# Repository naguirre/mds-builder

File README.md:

# Manufacture du Son

Open-source network audio player firmware. The board is built around an Allwinner **F1C200s** SoC running Linux and an **ESP32-C3** companion chip handling Wi-Fi and BLE. Audio is routed out over SPDIF.

📖 **Full documentation**: <https://naguirre.github.io/mds-builder/>

## Quick start

```sh
make build              # build firmware natively (Buildroot)
make build CONTAINER=1  # build inside the Docker container
```

Output images land in `output/images/`. See the [flashing guide](https://naguirre.github.io/mds-builder/flashing/) for getting them onto a board.

## Repository layout

- `buildroot_config/` — Buildroot defconfigs per machine
- `mds_external/` — `BR2_EXTERNAL` tree (boards, packages, overlays, FIT image)
- `mds-hardware/` — KiCad sources (see [mds-hardware/README.md](mds-hardware/README.md))
- `doc/` — Zola site, source for the published docs
- `src/esp-hosted/` — vendored ESP-Hosted sources

## Browsing the docs locally

```sh
cd doc && zola serve
```

## Hardware

The KiCad projects and PCB versions (v1, v1.1, v2) live under [`mds-hardware/`](mds-hardware/README.md). Schematics, PCB PDFs and gerbers are published alongside the documentation under `/hardware/<version>/`.

## License

- **Software** (this repository): MIT — see [LICENSE](LICENSE)
- **Hardware** (`mds-hardware/`): CERN-OHL-P v2 — see [mds-hardware/LICENSE](mds-hardware/LICENSE)

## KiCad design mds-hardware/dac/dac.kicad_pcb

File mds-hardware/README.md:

# mds-hardware

KiCad sources and fabrication outputs for a small network audio player board built around an Allwinner F1C200s SoC, an ESP32-C3 for Wi-Fi, NAND flash storage, an EA3036 power management IC, and an audio DAC daughter board.

The repository contains two KiCad projects:
- [network_player/](network_player/) — the main board
- [dac/](dac/) — the audio DAC daughter board

## Versions

| Version | Date       | Status                                             | Schematic | PCB | Gerbers |
|---------|------------|----------------------------------------------------|-----------|-----|---------|
| v1      | 2024-01-15 | Sent to JLCPCB, had routing issues                 | [PDF](../doc/static/hardware/v1/schematic.pdf) | [PDF](../doc/static/hardware/v1/pcb.pdf) | [ZIP](../doc/static/hardware/v1/gerbers.zip) |
| v1.1    | 2024-06-02 | Sent to JLCPCB, fixes routing issues of v1         | [PDF](../doc/static/hardware/v1.1/schematic.pdf) | [PDF](../doc/static/hardware/v1.1/pcb.pdf) | [ZIP](../doc/static/hardware/v1.1/gerbers.zip) |
| v2      | 2024-10-17 | Full redesign on Allwinner T113-s3, never produced | [PDF](../doc/static/hardware/v2/schematic.pdf) | [PDF](../doc/static/hardware/v2/pcb.pdf) | [ZIP](../doc/static/hardware/v2/gerbers.zip) |

See also the rendered [Board design](../doc/content/hardware/design.md) page in the main documentation.

References on GitHub: v1 is at commit [`c1560a5`](../../commit/c1560a5), v1.1 is the [`v1.1`](../../tree/v1.1) tag, v2 lives on the [`network_player_v2`](../../tree/network_player_v2) branch. The [`v1_jlcpcb`](../../tree/v1_jlcpcb) tag points to the JLCPCB return files for v1.

## Latest produced version: v1.1

v1.1 is the version that was actually fabricated and assembled by JLCPCB. Compared to v1, it brings the following changes (see commit [`47ae173`](../../commit/47ae173)):

- Removed the discrete transistors used for ESP32 boot/reset, driven directly from F1C200s GPIOs instead
- EA3036 enable pin tied to 3.3 V
- Added a RST button that pulls the MISO line to ground to disable booting from flash
- ESP32 moved to SPI1; SPI0 is now shared between the NAND flash and the RPi connector

### Schematic

## License

The hardware design (KiCad sources, schematics, PCB layouts and gerbers) is released under the **CERN Open Hardware Licence Version 2 — Permissive** (CERN-OHL-P v2). See [LICENSE](LICENSE).

Copyright (c) 2026 Nicolas Aguirre.

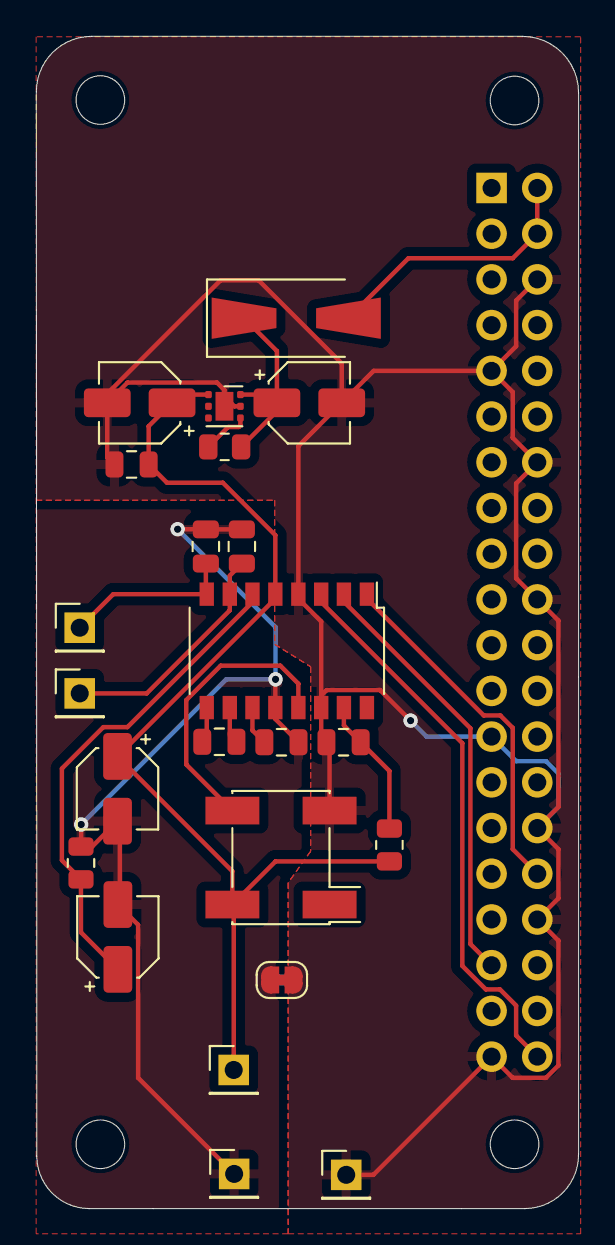
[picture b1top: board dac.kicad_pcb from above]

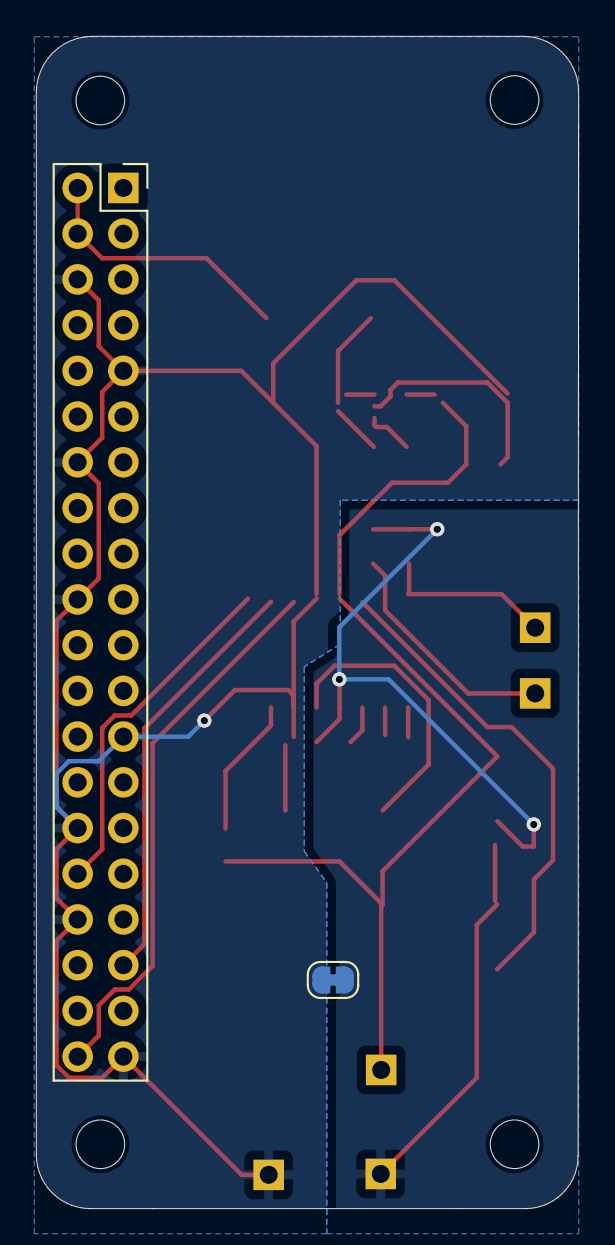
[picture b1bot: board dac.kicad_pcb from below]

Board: 2 copper layers, 30.1 x 65.1 mm, 29 parts (2 on the bottom side), 17 nets.

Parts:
C1: 2.2uF; C_0805_2012Metric
C2: 2.2uF/50V; CP_Elec_4x5.8
C3, C8, C9: 10uF/25V; CP_Elec_4x5.8
C4, C5, C10: 1uF; C_0805_2012Metric
C6, C7: 4.7nF; C_0805_2012Metric
D1: 1N5822/SS34/SMA; D_SMA-SMB_Universal_Handsoldering
H1, H2, H3, H4: MountingHole; MountingHole_2.7mm_M2.5
J1: Raspberry_Pi_2_3; PinSocket_2x20_P2.54mm_Vertical
J2: LEFT; PinHeader_1x01_P2.54mm_Vertical
J3: RIGHT; PinHeader_1x01_P2.54mm_Vertical
J6: 3v3; PinHeader_1x01_P2.54mm_Vertical
J7: GND; PinHeader_1x01_P2.54mm_Vertical
J8: GNDA; PinHeader_1x01_P2.54mm_Vertical
NT1, NT2: NetTie_2; SolderJumper-2_P1.3mm_Bridged_RoundedPad1.0x1.5mm
R1, R3: 100k; R_0805_2012Metric
R2: 220k; R_0805_2012Metric
U1: TCXO 49.152 MHz; Oscillator_SMD_Fordahl_DFAS11-4Pin_7.0x5.0mm_HandSoldering
U2: ES9023; SOP-16_4.4x10.4mm_P1.27mm
U5: LP5912-3.3DRV; WSON-6-1EP_2x2mm_P0.65mm_EP1x1.6mm

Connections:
+3V3: C2.1, C9.1, C10.1, J6.1, R1.2, U1.4 (VDD), U2.5 (AVCC), U5.1 (OUT)
+5V: D1.2 (A), J1.2 (5V), J1.4 (5V)
/AUDIO_LEFT: C7.1, J2.1, U2.7 (AOUTL)
/AUDIO_RIGHT: C6.1, J3.1, U2.8 (AOUTR)
/I2S_BCLK: J1.32 (PWM0/GPIO12), U2.1 (BCK)
/I2S_DOUT: J1.40 (GPIO21/SCLK1), U2.3 (SDI)
/I2S_LRCK: J1.35 (GPIO19/MISO1), U2.2 (LRCK)
/VIN: C8.1, D1.1 (K), R3.2, U5.6 (IN)
GND: C1.2, C8.2, C9.2, C10.2, J1.6 (GND), J1.9 (GND), J1.14 (GND), J1.20 (GND), J1.25 (GND), J1.30 (GND), J1.34 (GND), J1.39 (GND), J7.1, NT1.1, NT2.1, U1.2 (GND), U2.4 (DIF), U2.14 (DGND), U5.5 (GND), U5.7 (EP)
GNDA: C2.2, C3.2, C4.2, C6.2, C7.2, J8.1, NT1.2, NT2.2, R2.1, U2.12 (AGND)
unnamed: U1.3 (OUT), U2.13 (MCLK)
unnamed: C5.2, U2.10 (CN)
unnamed: C5.1, U2.9 (CP)
unnamed: C1.1, R1.1, U2.15 (MUTE_B)
unnamed: C4.1, U2.11 (NEG)
unnamed: C3.1, R2.2, U2.6 (VREG)
unnamed: R3.1, U5.4 (EN)

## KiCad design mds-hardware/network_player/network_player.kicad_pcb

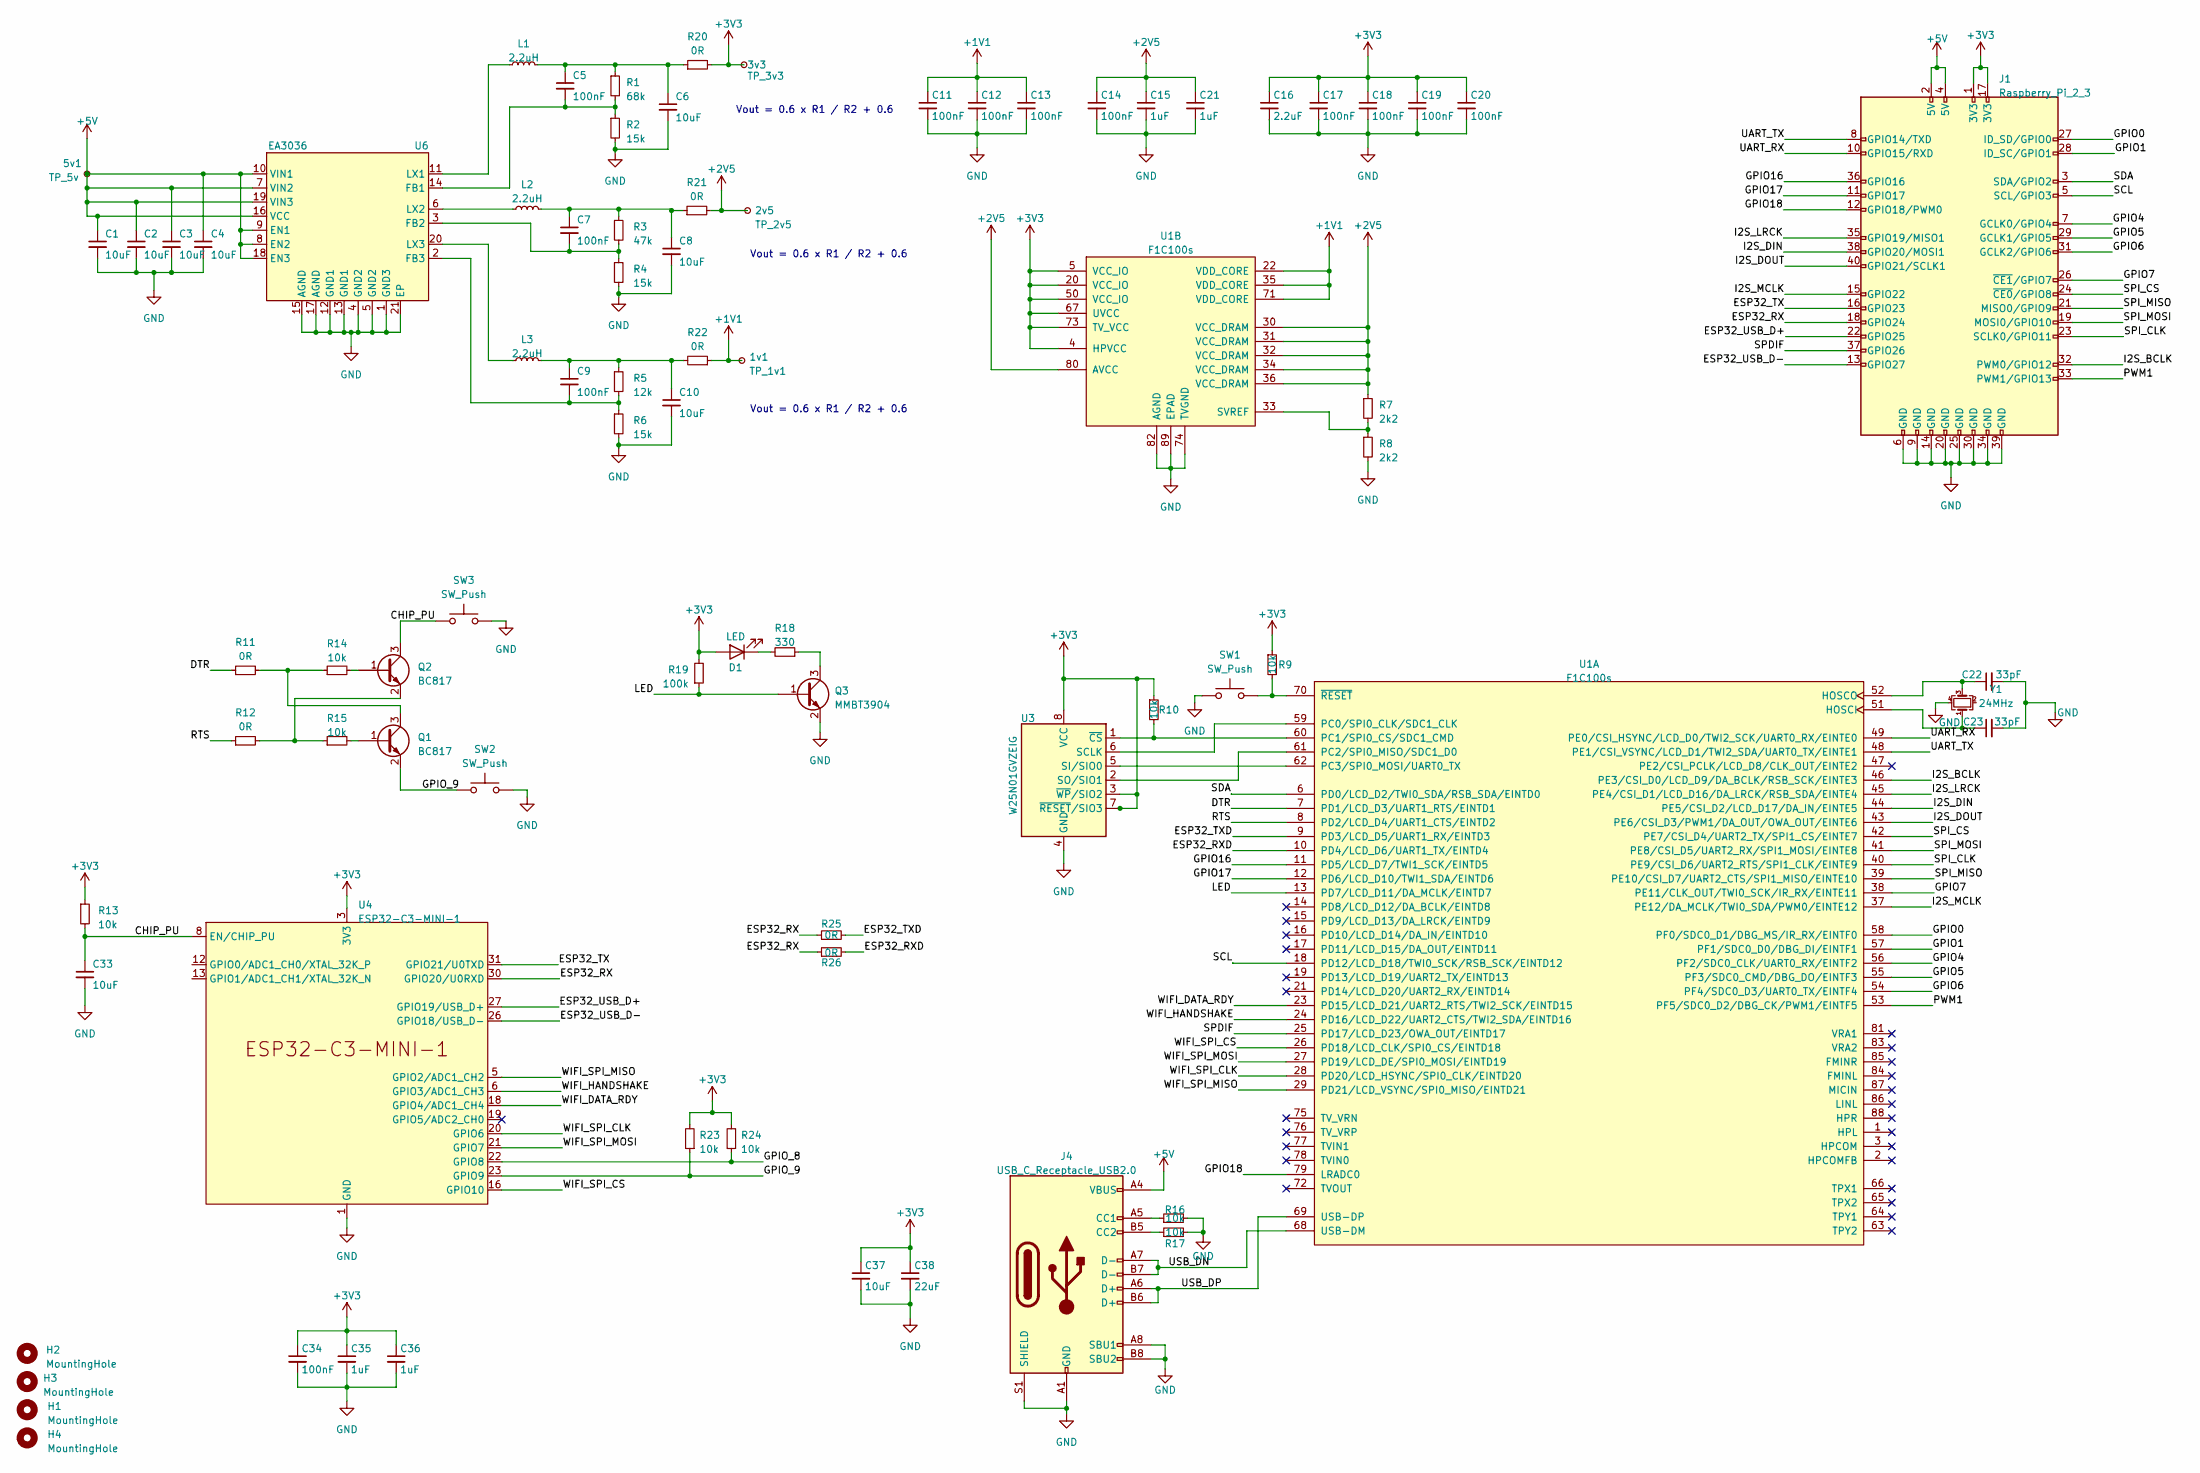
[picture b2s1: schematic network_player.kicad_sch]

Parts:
1v1: TP_1v1; TestPoint_Pad_D1.0mm
2v5: TP_2v5; TestPoint_Pad_D1.0mm
3v3: TP_3v3; TestPoint_Pad_D1.0mm
5v1: TP_5v; TestPoint_Pad_D1.0mm
C1, C2, C3, C4, C6, C8, C10, C33, C37: 10uF; C_0402_1005Metric; LCSC C15525
C5, C7, C9, C11, C12, C13, C14, C17, C18, C19, C20, C34: 100nF; C_0402_1005Metric; LCSC C307331
C15, C21, C35, C36: 1uF; C_0402_1005Metric; LCSC C52923
C16: 2.2uF; C_0402_1005Metric; LCSC C12530
C22, C23: 33pF; C_0402_1005Metric; LCSC C1562
C38: 22uF; C_0805_2012Metric; LCSC C59461
D1: LED; LED_0603_1608Metric
H1, H2, H3, H4: MountingHole; MountingHole_2.7mm_M2.5
J1: Raspberry_Pi_2_3; PinHeader_2x20_P2.54mm_Vertical
J4: USB_C_Receptacle_USB2.0; USB_C_Receptacle_GT-USB-7010; LCSC C963370
L1, L2, L3: 2.2uH; L_0805_2012Metric; LCSC C1043
Q1, Q2: BC817; SOT-23; LCSC C2150
Q3: MMBT3904; SOT-23; LCSC C20526
R1: 68k; R_0402_1005Metric; LCSC C36871
R2, R4, R6: 15k; R_0402_1005Metric; LCSC C25756
R3: 47k; R_0402_1005Metric; LCSC C25792
R5: 12k; R_0402_1005Metric; LCSC C25752
R7, R8: 2k2; R_0402_1005Metric; LCSC C25879
R9, R10, R13, R14, R15, R16, R17, R23, R24: 10k; R_0402_1005Metric; LCSC C25744
R11, R12, R20, R21, R22, R25, R26: 0R; R_0402_1005Metric; LCSC C17168
R18: 330; R_0402_1005Metric; LCSC C25104
R19: 100k; R_0402_1005Metric; LCSC C25741
SW1, SW2, SW3: SW_Push; SW_Push_1P1T_XKB_TS-1187A; LCSC C318884
U1: F1C100s; QFN-88_EP_10x10_Pitch0.4mm; LCSC C2879851
U3: W25N01GVZEIG; WSON-8-1EP_8x6mm_P1.27mm_EP3.4x4.3mm; LCSC C88868
U4: ESP32-C3-MINI-1; LCSC C2838502
U6: EA3036; QFN-20-1EP_3x3mm_P0.4mm_EP1.65x1.65mm; LCSC C570857
Y1: 24MHz; Crystal_SMD_SeikoEpson_TSX3225-4Pin_3.2x2.5mm; LCSC C15643

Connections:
+1V1: 1v1.1, C11.1, C12.1, C13.1, R22.1, U1.22 (VDD_CORE), U1.35 (VDD_CORE), U1.71 (VDD_CORE)
+2V5: 2v5.1, C14.1, C15.1, C21.1, R7.1, R21.2, U1.30 (VCC_DRAM), U1.31 (VCC_DRAM), U1.32 (VCC_DRAM), U1.34 (VCC_DRAM), U1.36 (VCC_DRAM), U1.80 (AVCC)
+3V3: 3v3.1, C16.1, C17.1, C18.1, C19.1, C20.1, C34.1, C35.1, C36.1, C37.1, C38.1, D1.2 (A), J1.1 (3V3), J1.17 (3V3), R9.1, R10.1, R13.1, R19.2, R20.2, R23.2, R24.2, U1.4 (HPVCC), U1.5 (VCC_IO), U1.20 (VCC_IO), U1.50 (VCC_IO), U1.67 (UVCC), U1.73 (TV_VCC), U3.3 (~WP/SIO2), U3.7 (~RESET/SIO3), U3.8 (VCC), U4.3 (3V3)
+5V: 5v1.1, C1.1, C2.1, C3.1, C4.1, J1.2 (5V), J1.4 (5V), J4.A4 (VBUS), J4.A9 (VBUS), J4.B4 (VBUS), J4.B9 (VBUS), U6.7 (VIN2), U6.8 (EN2), U6.9 (EN1), U6.10 (VIN1), U6.16 (VCC), U6.18 (EN3), U6.19 (VIN3)
/CHIP_PU: C33.1, Q2.3 (C), R13.2, SW3.1, U4.8 (EN/CHIP_PU)
/DTR: R11.1, U1.7 (PD1/LCD_D3/UART1_RTS/EINTD1)
/ESP32_RX: J1.18 (GPIO24), R25.1, R26.1, U4.30 (GPIO20/U0RXD)
/ESP32_RXD: R26.2, U1.10 (PD4/LCD_D6/UART1_TX/EINTD4)
/ESP32_TX: J1.16 (GPIO23), U4.31 (GPIO21/U0TXD)
/ESP32_TXD: R25.2, U1.9 (PD3/LCD_D5/UART1_RX/EINTD3)
/ESP32_USB_D+: J1.22 (GPIO25), U4.27 (GPIO19/USB_D+)
/ESP32_USB_D-: J1.13 (GPIO27), U4.26 (GPIO18/USB_D-)
/GPIO0: J1.27 (ID_SD/GPIO0), U1.58 (PF0/SDC0_D1/DBG_MS/IR_RX/EINTF0)
/GPIO1: J1.28 (ID_SC/GPIO1), U1.57 (PF1/SDC0_D0/DBG_DI/EINTF1)
/GPIO4: J1.7 (GCLK0/GPIO4), U1.56 (PF2/SDC0_CLK/UART0_RX/EINTF2)
/GPIO5: J1.29 (GCLK1/GPIO5), U1.55 (PF3/SDC0_CMD/DBG_DO/EINTF3)
/GPIO6: J1.31 (GCLK2/GPIO6), U1.54 (PF4/SDC0_D3/UART0_TX/EINTF4)
/GPIO7: J1.26 (~CE1/GPIO7), U1.38 (PE11/CLK_OUT/TWI0_SCK/IR_RX/EINTE11)
/GPIO16: J1.36 (GPIO16), U1.11 (PD5/LCD_D7/TWI1_SCK/EINTD5)
/GPIO17: J1.11 (GPIO17), U1.12 (PD6/LCD_D10/TWI1_SDA/EINTD6)
/GPIO18: J1.12 (GPIO18/PWM0), U1.79 (LRADC0)
/GPIO_8: R24.1, U4.22 (GPIO8)
/GPIO_9: Q1.2 (E), R23.1, SW2.1, U4.23 (GPIO9)
/I2S_BCLK: J1.32 (PWM0/GPIO12), U1.46 (PE3/CSI_D0/LCD_D9/DA_BCLK/RSB_SCK/EINTE3)
/I2S_DIN: J1.38 (GPIO20/MOSI1), U1.44 (PE5/CSI_D2/LCD_D17/DA_IN/EINTE5)
/I2S_DOUT: J1.40 (GPIO21/SCLK1), U1.43 (PE6/CSI_D3/PWM1/DA_OUT/OWA_OUT/EINTE6)
/I2S_LRCK: J1.35 (GPIO19/MISO1), U1.45 (PE4/CSI_D1/LCD_D16/DA_LRCK/RSB_SDA/EINT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)
/I2S_MCLK: J1.15 (GPIO22), U1.37 (PE12/DA_MCLK/TWI0_SDA/PWM0/EINTE12)
/LED: Q3.1 (B), R19.1, U1.13 (PD7/LCD_D11/DA_MCLK/EINTD7)
/PWM1: J1.33 (PWM1/GPIO13), U1.53 (PF5/SDC0_D2/DBG_CK/PWM1/EINTF5)
/RTS: R12.1, U1.8 (PD2/LCD_D4/UART1_CTS/EINTD2)
/SCL: J1.5 (SCL/GPIO3), U1.18 (PD12/LCD_D18/TWI0_SCK/RSB_SCK/EINTD12)
/SDA: J1.3 (SDA/GPIO2), U1.6 (PD0/LCD_D2/TWI0_SDA/RSB_SDA/EINTD0)
/SPDIF: J1.37 (GPIO26), U1.25 (PD17/LCD_D23/OWA_OUT/EINTD17)
/SPI_CLK: J1.23 (SCLK0/GPIO11), U1.40 (PE9/CSI_D6/UART2_RTS/SPI1_CLK/EINTE9)
/SPI_CS: J1.24 (~CE0/GPIO8), U1.42 (PE7/CSI_D4/UART2_TX/SPI1_CS/EINTE7)
/SPI_MISO: J1.21 (MISO0/GPIO9), U1.39 (PE10/CSI_D7/UART2_CTS/SPI1_MISO/EINTE10)
/SPI_MOSI: J1.19 (MOSI0/GPIO10), U1.41 (PE8/CSI_D5/UART2_RX/SPI1_MOSI/EINTE8)
/UART_RX: J1.10 (GPIO15/RXD), U1.49 (PE0/CSI_HSYNC/LCD_D0/TWI2_SCK/UART0_RX/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)
/UART_TX: J1.8 (GPIO14/TXD), U1.48 (PE1/CSI_VSYNC/LCD_D1/TWI2_SDA/UART0_TX/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)
/USB_DN: J4.A7 (D-), J4.B7 (D-), U1.68 (USB-DM)
/USB_DP: J4.A6 (D+), J4.B6 (D+), U1.69 (USB-DP)
/WIFI_DATA_RDY: U1.23 (PD15/LCD_D21/UART2_RTS/TWI2_SCK/EINTD15), U4.18 (GPIO4/ADC1_CH4)
/WIFI_HANDSHAKE: U1.24 (PD16/LCD_D22/UART2_CTS/TWI2_SDA/EINTD16), U4.6 (GPIO3/ADC1_CH3)
/WIFI_SPI_CLK: U1.28 (PD20/LCD_HSYNC/SPI0_CLK/EINTD20), U4.20 (GPIO6)
/WIFI_SPI_CS: U1.26 (PD18/LCD_CLK/SPI0_CS/EINTD18), U4.16 (GPIO10)
/WIFI_SPI_MISO: U1.29 (PD21/LCD_VSYNC/SPI0_MISO/EINTD21), U4.5 (GPIO2/ADC1_CH2)
/WIFI_SPI_MOSI: U1.27 (PD19/LCD_DE/SPI0_MOSI/EINTD19), U4.21 (GPIO7)
GND: C1.2, C2.2, C3.2, C4.2, C6.2, C8.2, C10.2, C11.2, C12.2, C13.2, C14.2, C15.2, C16.2, C17.2, C18.2, C19.2, C20.2, C21.2, C22.2, C23.2, C33.2, C34.2, C35.2, C36.2, C37.2, C38.2, J1.6 (GND), J1.9 (GND), J1.14 (GND), J1.20 (GND), J1.25 (GND), J1.30 (GND), J1.34 (GND), J1.39 (GND), J4.A1 (GND), J4.A8 (SBU1), J4.A12 (GND), J4.B1 (GND), J4.B8 (SBU2), J4.B12 (GND), J4.S1 (SHIELD), Q3.2 (E), R2.2, R4.2, R6.2, R8.2, R16.2, R17.2, SW1.1, SW2.2, SW3.2, U1.74 (TVGND), U1.82 (AGND), U1.89 (EPAD), U3.4 (GND), U3.9 (GND), U4.1 (GND), U4.2 (GND), U4.11 (GND), U4.14 (GND), U4.36 (GND), U4.37 (GND), U4.38 (GND), U4.39 (GND), U4.40 (GND), U4.41 (GND), U4.42 (GND), U4.43 (GND), U4.44 (GND), U4.45 (GND), U4.46 (GND), U4.47 (GND), U4.48 (GND), U4.49 (GND), U4.50 (GND), U4.51 (GND), U4.52 (GND), U4.53 (GND), U6.1 (GND3), U6.4 (GND2), U6.5 (GND2), U6.12 (GND1), U6.13 (GND1), U6.15 (AGND), U6.17 (AGND), U6.21 (EP), Y1.4
unnamed: C5.1, C6.1, L1.2, R1.1, R20.1
unnamed: C7.1, C8.1, L2.2, R3.1, R21.1
unnamed: C9.1, C10.1, L3.2, R5.1, R22.2
unnamed: D1.1 (K), R18.2
unnamed: J4.A5 (CC1), R16.1
unnamed: J4.B5 (CC2), R17.1
unnamed: Q1.1 (B), R15.2
unnamed: Q1.3 (C), R11.2, R14.1
unnamed: Q2.1 (B), R14.2
unnamed: Q2.2 (E), R12.2, R15.1
unnamed: Q3.3 (C), R18.1
unnamed: C23.1, U1.51 (HOSCI), Y1.1
unnamed: C22.1, U1.52 (HOSCO), Y1.3
unnamed: U1.59 (PC0/SPI0_CLK/SDC1_CLK), U3.6 (SCLK)
unnamed: R10.2, U1.60 (PC1/SPI0_CS/SDC1_CMD), U3.1 (~CS)
unnamed: U1.61 (PC2/SPI0_MISO/SDC1_D0), U3.2 (SO/SIO1)
unnamed: U1.62 (PC3/SPI0_MOSI/UART0_TX), U3.5 (SI/SIO0)
unnamed: R9.2, SW1.2, U1.70 (~RESET)
unnamed: R7.2, R8.1, U1.33 (SVREF)
unnamed: C5.2, R1.2, R2.1, U6.14 (FB1)
unnamed: C7.2, R3.2, R4.1, U6.3 (FB2)
unnamed: C9.2, R5.2, R6.1, U6.2 (FB3)
unnamed: L1.1, U6.11 (LX1)
unnamed: L2.1, U6.6 (LX2)
unnamed: L3.1, U6.20 (LX3)

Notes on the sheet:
Vout = 0.6 x R1 / R2 + 0.6

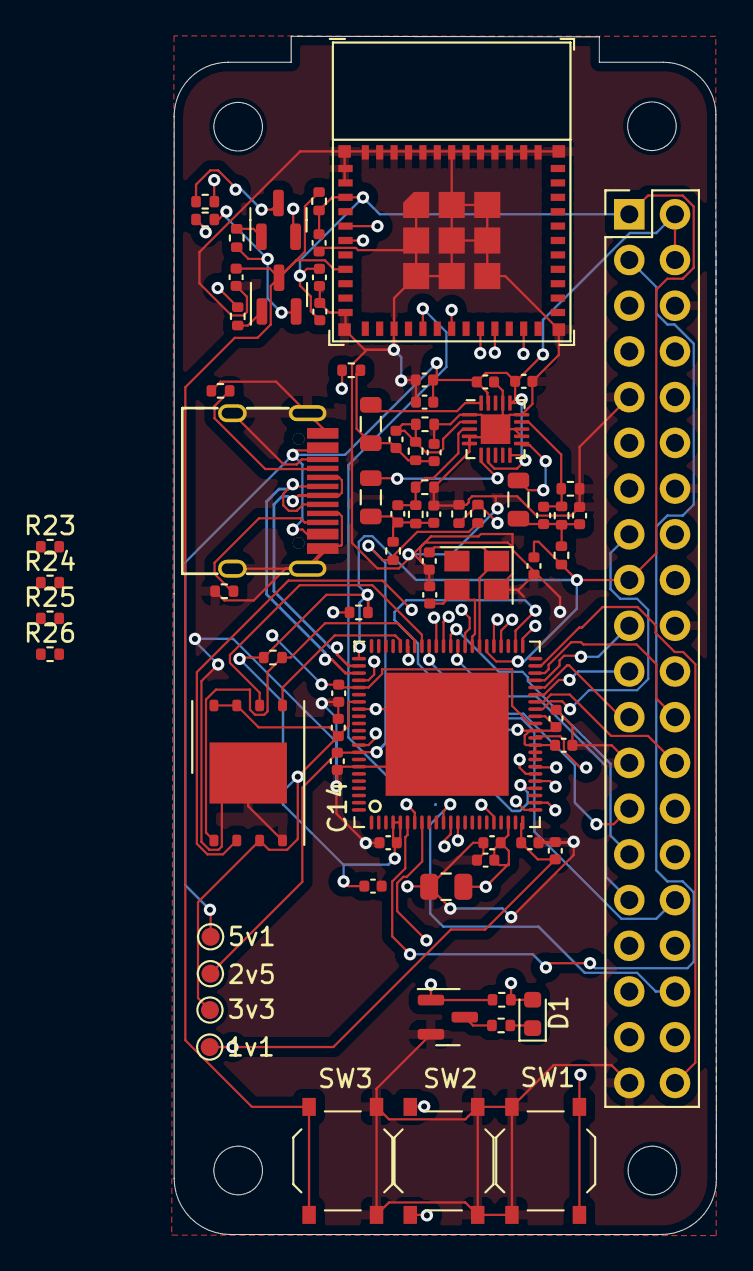
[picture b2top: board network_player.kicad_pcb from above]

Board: 4 copper layers, 30.1 x 66.6 mm, 80 parts (0 on the bottom side), 74 nets.

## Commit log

2025-10-05 remove unused packages
2025-10-05 avoid pushing all the context in Docker contianer
2026-05-10 add more configs
2026-05-25 doc: migrate to Zola with Goyo theme
2026-05-25 build: bump Buildroot to 2026.02.1 and U-Boot to 2026.04
2026-05-25 uboot: drop last patch and simplify mknandboot.sh
2026-05-27 doc: merge mds-hardware artifacts into Zola doc
    Move v1/v1.1/v2 hardware artifacts to doc/static/hardware/, merge KiCad
    page into hardware/design.md with version table, replace architecture
    ASCII art with a Mermaid diagram, and fix highlight_code config for
    Zola 0.22.
2026-05-27 doc: rewrite README, add MIT/CERN-OHL licenses, custom Zola theme, deploy workflow
2026-05-27 build: stop tracking local.mk so CI uses upstream sources
2026-05-27 build: re-pin esp-hosted via tracked overrides.mk and drop unused submodules
2026-05-27 ci: fix build-docker workflow and use ghcr image in build-mds
2026-05-27 doc: fix internal links broken on GitHub Pages subpaths
2026-05-27 theme: route card shortcode href through get_url for subpath hosting
2026-05-31 build: bump uboot to 2026.04 and switch kernel to custom linux-sunxi git tree
2026-05-31 build: drop trailing blank line in overrides.mk
2026-05-31 build(images): warn when uImage or initramfs outgrows its FEL RAM budget
2026-05-31 feat(bootstrap): rewrite bootstrap.sh to auto-provision NAND over SSH and add makeself bundle
2026-05-31 docs(hardware): add photos of assembled v1.0 and v1.1 boards
2026-05-31 docs(flashing): document automated bootstrap + NAND provisioning and RAM layout
2026-05-31 docs(conference): add presenterm talk for Toulouse Embedded Meetup June 2026
2026-06-16 doc(conference): add more materials
2026-06-16 doc(conference): more doc

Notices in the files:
mds-hardware/network_player/network_player.kicad_pcb:
(c) 2024
